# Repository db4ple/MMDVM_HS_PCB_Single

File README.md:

# MMDVM_HS_PCB_Single
Single Sided PCB for MMDVM Hotspot with RF7021SE module and Blue Pill STM32DUINO

This project provides a simple, singled sided PCB for the [MMDVM_HS Hotspot main repo](https://github.com/juribeparada/MMDVM_HS). 
Can be easily made using toner transfer, has very few wires. Just order the components (RF7021SE from Aliexpress and Blue Pill 
STM32DUINO clone) and put on board. Do not forget to replace the RF7021SE standard oscillator with a supported TCXO.

The second pcb design called stick is much smaller, and has a more logical led layout. But it requires a few more via wires if made as a single sided board. 
Most connecting wires are only used if the optional connectors are used. 
The single pin connector in the middle of the board is in fact a bottom / top ground plane connection for a two sided design. No need to use it on a single sided pcb.

© DB4PLE
Licensed under CC-BY-SA 3.0

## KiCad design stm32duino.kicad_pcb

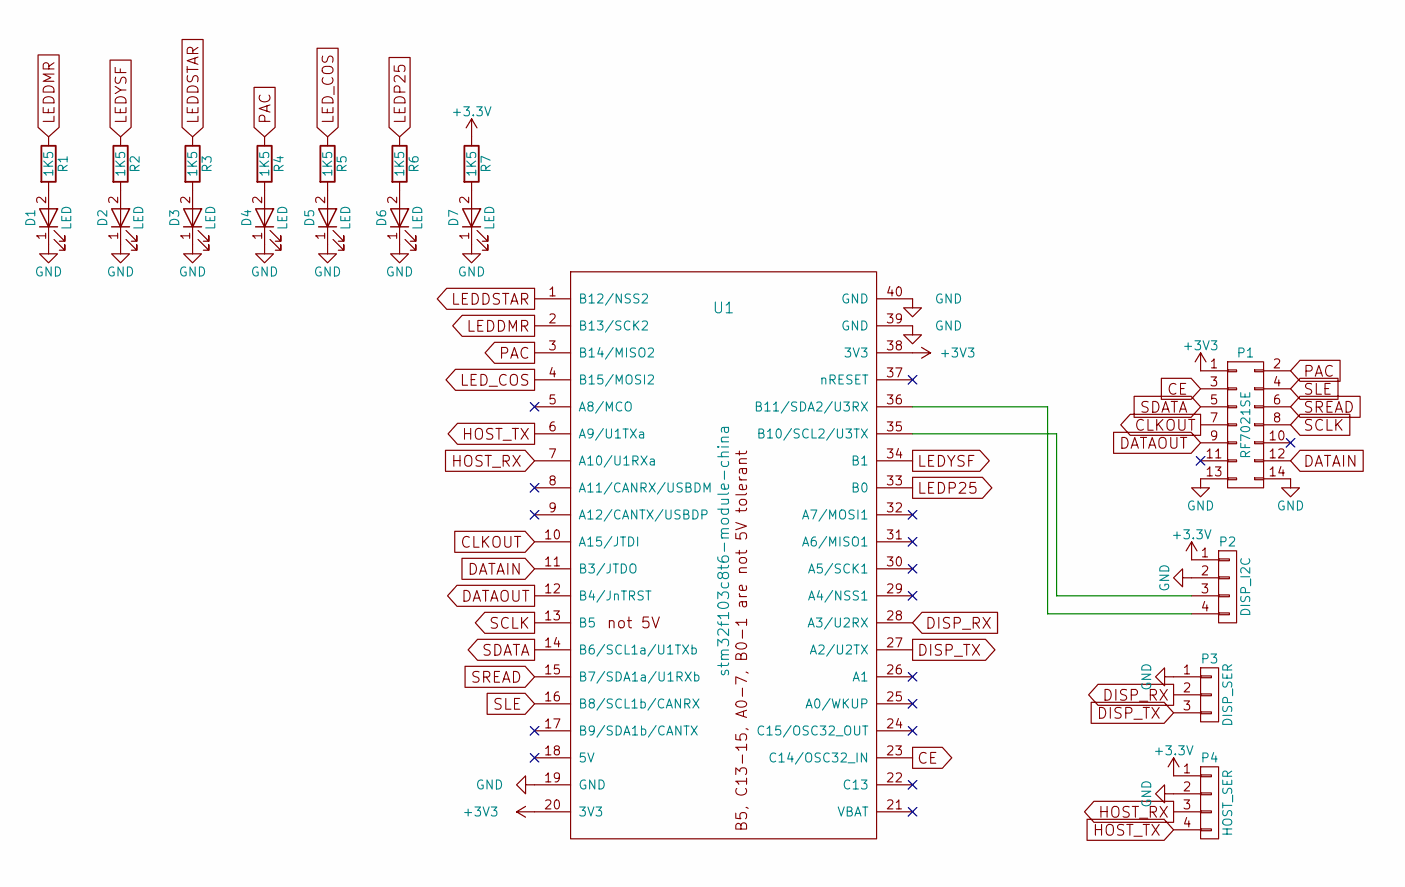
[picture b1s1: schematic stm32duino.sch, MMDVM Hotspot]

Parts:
D1, D2, D3, D4, D5, D6, D7: LED; LED_0805
P1: RF7021SE; Pin_Header_Straight_2x07_Pitch2.54mm
P2: DISP_I2C; Pin_Header_Angled_1x04_Pitch2.54mm
P3: DISP_SER; Pin_Header_Angled_1x03_Pitch2.54mm
P4: HOST_SER; Pin_Header_Angled_1x04_Pitch2.54mm
R1, R2, R3, R4, R5, R6, R7: 1K5; R_0805
U1: stm32f103c8t6-module-china

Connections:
CE: P1.3, U1.23 (C14/OSC32_IN)
CLKOUT: P1.7, U1.10 (A15/JTDI)
DATAIN: P1.12, U1.11 (B3/JTDO)
DATAOUT: P1.9, U1.12 (B4/JnTRST)
DISP_RX: P3.2, U1.28 (A3/U2RX)
DISP_TX: P3.3, U1.27 (A2/U2TX)
GND: D1.1 (K), D2.1 (K), D3.1 (K), D4.1 (K), D5.1 (K), D6.1 (K), D7.1 (K), P1.13, P1.14, P2.2, P3.1, P4.2, U1.19 (GND), U1.39 (GND), U1.40 (GND)
HOST_RX: P4.3, U1.7 (A10/U1RXa)
HOST_TX: P4.4, U1.6 (A9/U1TXa)
LEDDMR: R1.1, U1.2 (B13/SCK2)
LEDDSTAR: R3.1, U1.1 (B12/NSS2)
LEDP25: R6.1, U1.33 (B0)
LEDYSF: R2.1, U1.34 (B1)
LED_COS: R5.1, U1.4 (B15/MOSI2)
unnamed: D1.2 (A), R1.2
unnamed: D2.2 (A), R2.2
unnamed: D3.2 (A), R3.2
unnamed: D4.2 (A), R4.2
unnamed: D5.2 (A), R5.2
unnamed: D6.2 (A), R6.2
unnamed: D7.2 (A), R7.2
unnamed: P2.3, U1.35 (B10/SCL2/U3TX)
unnamed: P2.4, U1.36 (B11/SDA2/U3RX)
PAC: P1.2, R4.1, U1.3 (B14/MISO2)
SCLK: P1.8, U1.13 (B5)
SDATA: P1.5, U1.14 (B6/SCL1a/U1TXb)
SLE: P1.4, U1.16 (B8/SCL1b/CANRX)
SREAD: P1.6, U1.15 (B7/SDA1a/U1RXb)

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
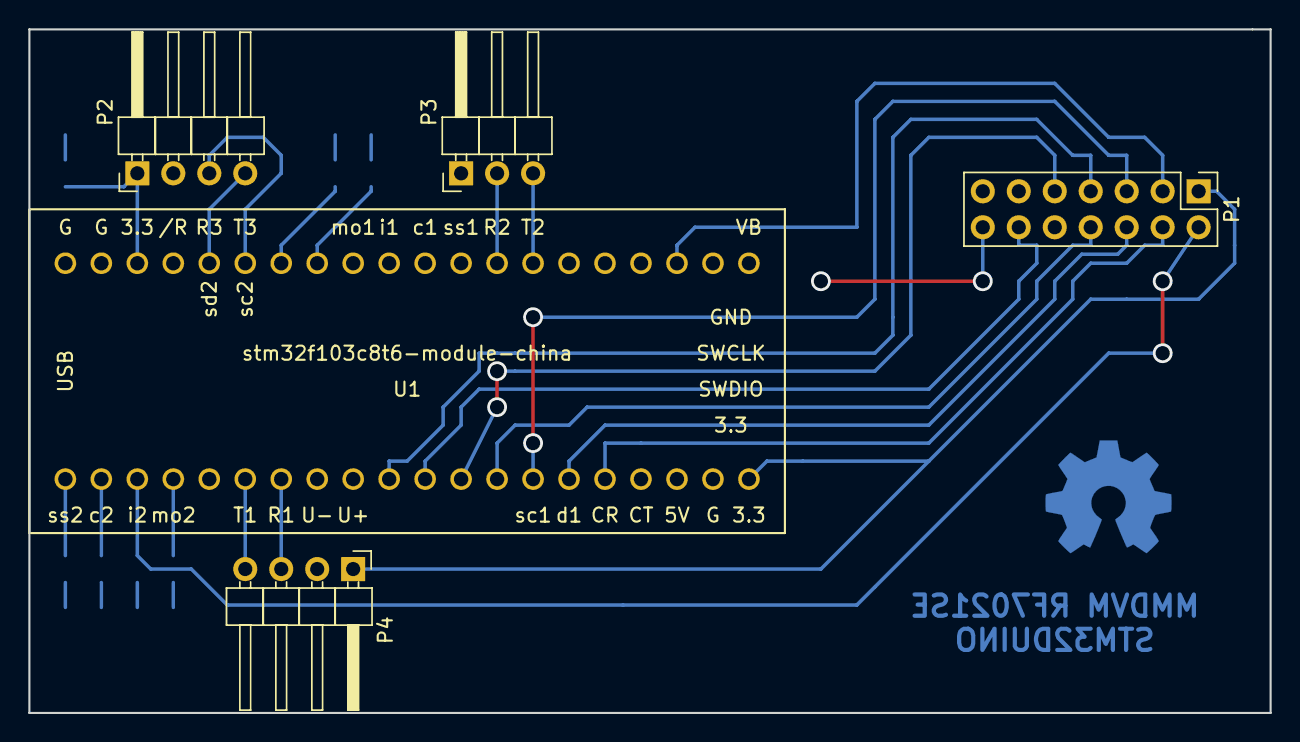
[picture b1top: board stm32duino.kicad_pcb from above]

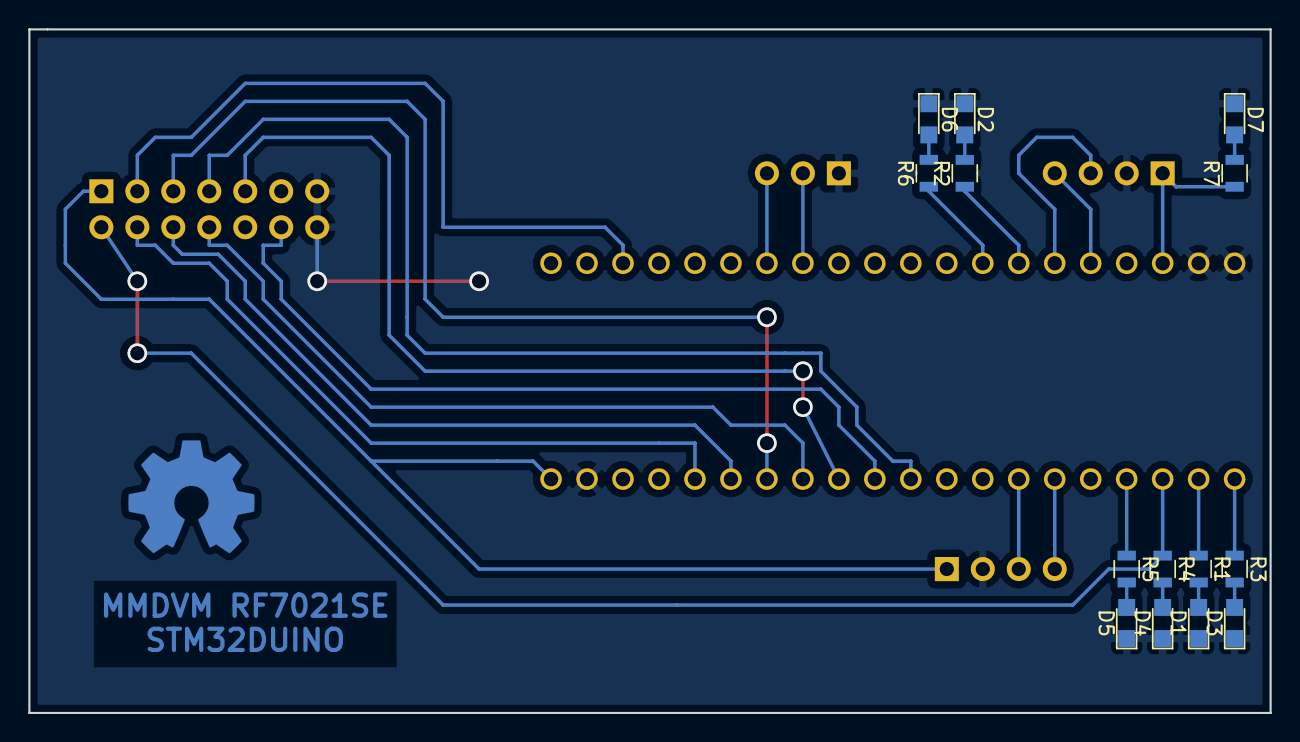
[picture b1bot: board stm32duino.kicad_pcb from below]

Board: 2 copper layers, 87.6 x 48.3 mm, 19 parts (14 on the bottom side), 29 nets.

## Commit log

2017-04-02 Init
2017-04-06 Minor beautification, added OSHW logo to PCB
2017-04-06 Added case design
2017-04-13 Added some more case components including a base containing an Pi Zero W which makes a nice selfcontained Hotspot.
    The additional PCB design is much smaller (a bit longer, though) and
    can be used to build a fairly compact hotspot. No case yet, not even build yet.
2017-05-08 Changed case to hold RPI Zero internally. Case may be a little to wide for machined boards, in this case adjust pcb_l after test print of some millimeters of height.
2017-08-22 Added placement and schematic pdf
2017-12-23 Added smaller footprint board which is NOT singlesided if you want the serial display or I2C display However, very few simple wires will do the job if you don't have the ability to do a two sided PCB.
2017-12-24 Finalized new "stick" design. Added gerbers.

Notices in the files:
stm32duino.sch:
Creative Commons CC by SA NC
